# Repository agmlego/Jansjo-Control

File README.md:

Jansjo-Control
==============

AVR-based smart controller for the IKEA Jansjo LED gooseneck desk lamp.

As designed:
* Provides three LED outputs
* Three manual switches
* Ambient light-sensing via CdS cell
* Occupancy by a Sharp IR proximity sensor
* Debug output via pogo-pin UART breakout pads at 0.1" spacing
* ISP via [TagConnect](http://www.tag-connect.com) footprint for board size

Firmware OSS under MIT License, hardware OSHW and in the public domain.

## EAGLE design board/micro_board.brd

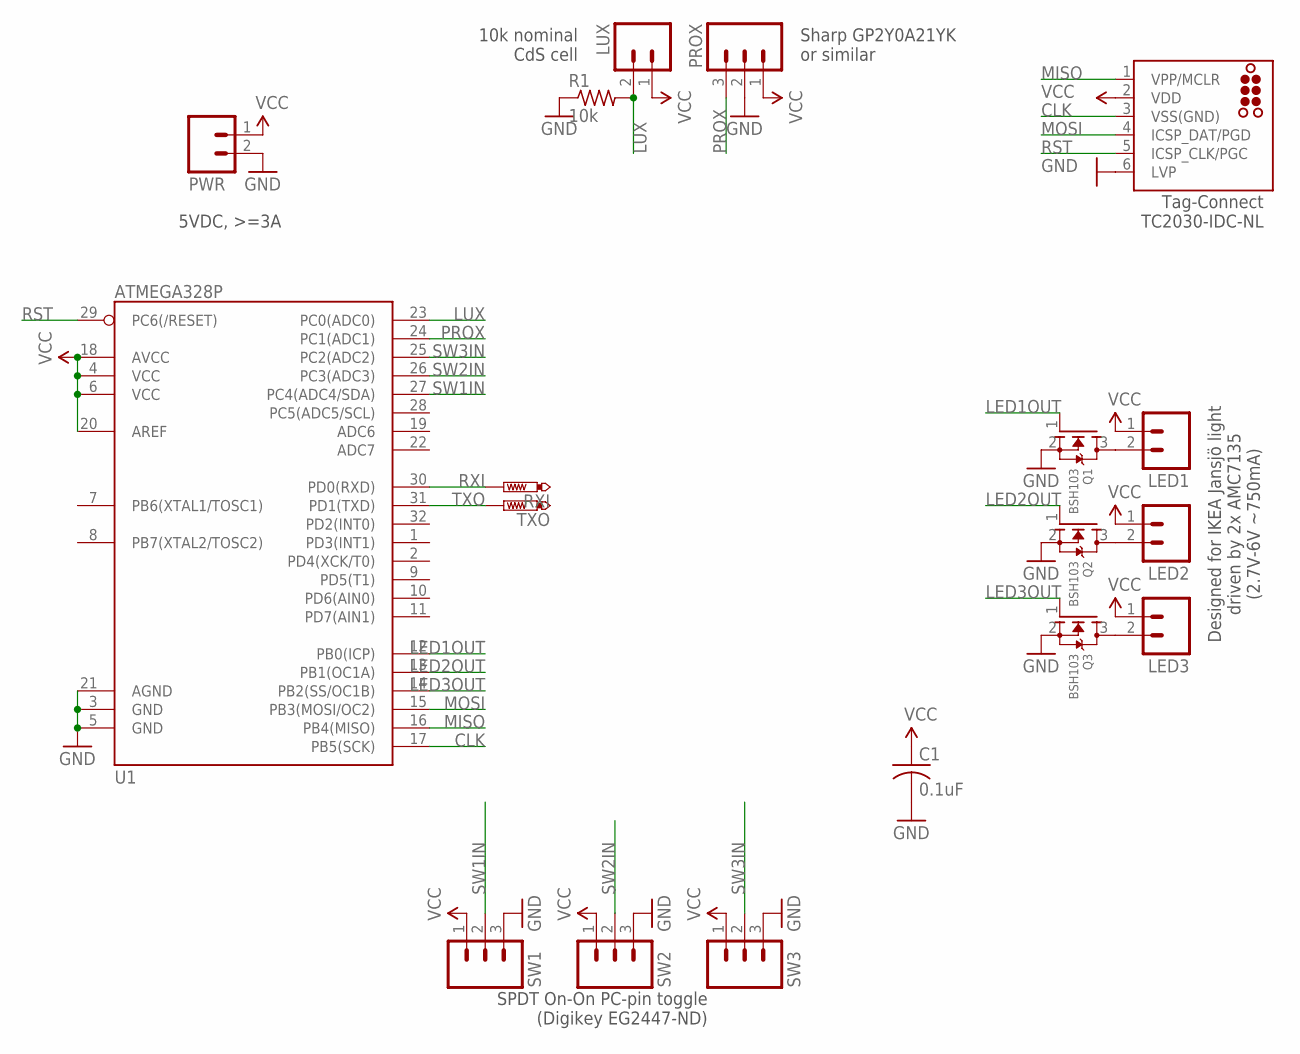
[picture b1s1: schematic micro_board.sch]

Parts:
C1: 0.1uF; C0603
J1: TC2030-MCP-NL
LED1, LED2, LED3: M02POLAR_LOCK; MOLEX-1X2_LOCK
LUX: M02POLAR_LOCK; MOLEX-1X2_LOCK
PROX: M03POLAR_LOCK; MOLEX-1X3_LOCK
PWR: M02POLAR_LOCK; MOLEX-1X2_LOCK
Q1, Q2, Q3: BSH103; SOT23
R1: 10k; R0603
RXI: PTR1B1,27; B1,27
SW1, SW2, SW3: M031X03_NO_SILK; 1X03_NO_SILK
TXO: PTR1B1,27; B1,27
U1: ATMEGA328P; TQFP32-08

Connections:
CLK: J1.3 (VSS(GND)), U1.17 (PB5(SCK))
GND: C1.2, J1.6 (LVP), PROX.2, PWR.2, Q1.2 (S), Q2.2 (S), Q3.2 (S), R1.1, SW1.3, SW2.3, SW3.3, U1.3 (GND), U1.5 (GND), U1.21 (AGND)
LED1OUT: Q1.1 (G), U1.12 (PB0(ICP))
LED2OUT: Q2.1 (G), U1.13 (PB1(OC1A))
LED3OUT: Q3.1 (G), U1.14 (PB2(SS/OC1B))
LUX: LUX.2, R1.2, U1.23 (PC0(ADC0))
MISO: J1.1 (VPP/MCLR), U1.16 (PB4(MISO))
MOSI: J1.4 (ICSP_DAT/PGD), U1.15 (PB3(MOSI/OC2))
unnamed: LED1.2, Q1.3 (D)
unnamed: LED2.2, Q2.3 (D)
unnamed: LED3.2, Q3.3 (D)
PROX: PROX.3, U1.24 (PC1(ADC1))
RST: J1.5 (ICSP_CLK/PGC), U1.29 (PC6(/RESET))
RXI: RXI.TP, U1.30 (PD0(RXD))
SW1IN: SW1.2, U1.27 (PC4(ADC4/SDA))
SW2IN: SW2.2, U1.26 (PC3(ADC3))
SW3IN: SW3.2, U1.25 (PC2(ADC2))
TXO: TXO.TP, U1.31 (PD1(TXD))
VCC: C1.1, J1.2 (VDD), LED1.1, LED2.1, LED3.1, LUX.1, PROX.1, PWR.1, SW1.1, SW2.1, SW3.1, U1.4 (VCC), U1.6 (VCC), U1.18 (AVCC), U1.20 (AREF)

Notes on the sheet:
Sharp GP2Y0A21YK or similar
10k nominal CdS cell
5VDC, >=3A
Designed for IKEA Jansjö light driven by 2x AMC7135 (2.7V-6V ~750mA)
Tag-Connect TC2030-IDC-NL
SPDT On-On PC-pin toggle (Digikey EG2447-ND)

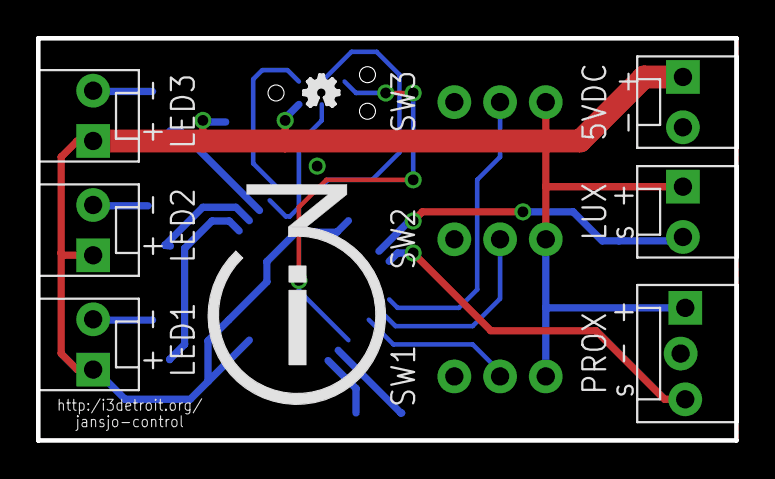
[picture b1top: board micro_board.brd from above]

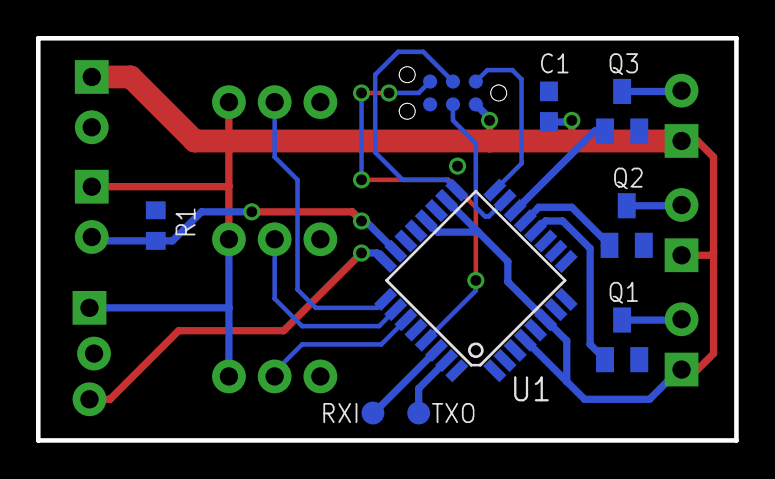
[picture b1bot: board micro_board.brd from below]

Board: 2 copper layers, 38.8 x 22.3 mm, 19 parts (9 on the bottom side), 19 nets.

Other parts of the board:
U$1: OSHW_FILLX70_NOTEXT

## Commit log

2014-04-17 Initial local commit.
2014-11-13 Edited board to use ATMEGA*8P 32-TQFP in place of ATTINY2313A, due to latter's lack of ADC channels needed for ambient illumination and proximity sensors.

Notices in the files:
parts and their libraries:
tag-connect: ©2009 ROFA.cz - modified and updated by Robert Darlington ‹rdarlington@gmail.com›
SparkFun-DigitalIC: Licensing: CC v3.0 Share-Alike You are welcome to use this library for commercial purposes.
